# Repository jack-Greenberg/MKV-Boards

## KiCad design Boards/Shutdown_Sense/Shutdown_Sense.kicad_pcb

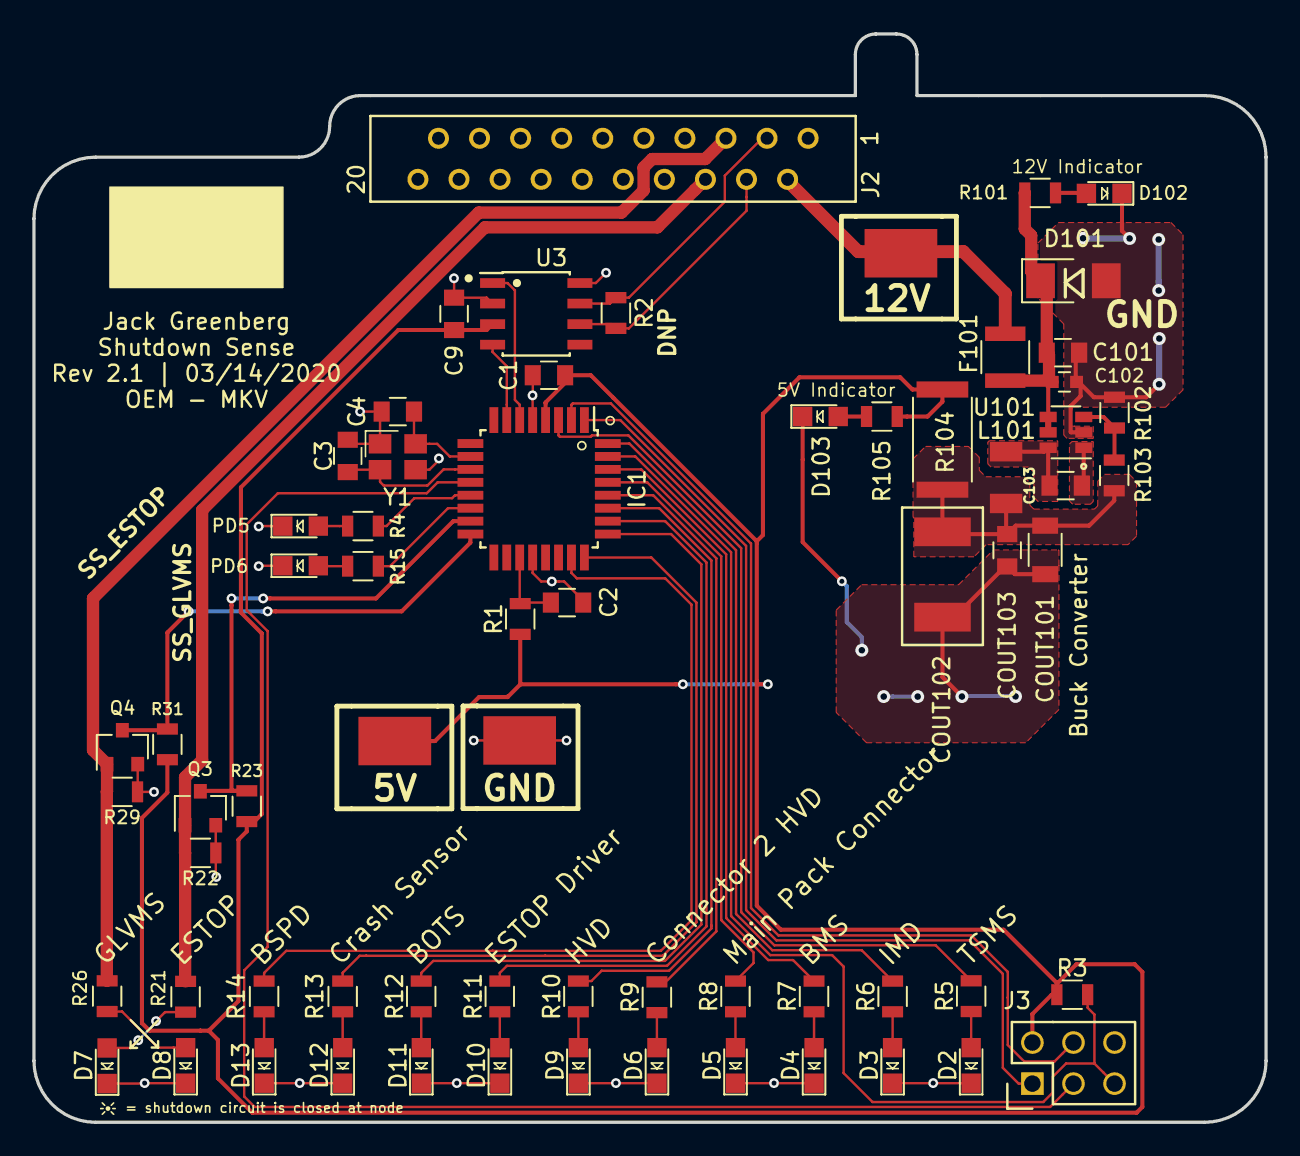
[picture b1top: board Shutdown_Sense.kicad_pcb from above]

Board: 2 copper layers, 76.2 x 67.3 mm, 67 parts (0 on the bottom side), 51 nets.

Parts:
C1, C9, C101, C103: C_0.1uF; C_0805_OEM
C2: C_100pF; C_0805_OEM
C3, C4: C_30pF; C_0805_OEM
C102: C_2.2uF; C_0603
COUT101: C_22uF; C_1206_OEM
COUT102: C_33uF; Fuse_1812
COUT103: C_47uF; C_0805_OEM
D2, D3, D4, D5, D6, D7, D8, D9, D10, D11, D12, D13, D102, D103: LED_0805; LED_0805_OEM
D101: D_Zener_18V; DO-214AA
F101: F_500mA_16V; Fuse_1210
IC1: ATMEGA16M1; TQFP-32_7x7mm_Pitch0.8mm
J2: MM_F_RA_20; micromatch_female_ra_20
J3: CONN_02X03; Pin_Header_Straight_2x03
L101: L_100uH
PD5, PD6: LED_0805; LED_0805_OEM
Q3, Q4: SSM3K333R; SOT-23F
R1: R_100; R_0805_OEM
R2: R_120_DNP; R_0805_OEM
R3: R_10k; R_0805_OEM
R4, R5, R6, R7, R8, R9, R10, R11, R12, R13, R14, R15, R105: R_200; R_0805_OEM
R21, R26, R101: R_1K; R_0805_OEM
R22, R29, R103: R_100K; R_0805_OEM
R23, R31: R_10K; R_0805_OEM
R102: R_25K; R_0805_OEM
R104: R_0_2512; R_2512_OEM
TP1, TP2, TP3: Test_Point_SMD
U3: CAN_Transceiver; SOIC-8_3.9x4.9mm_Pitch1.27mm_OEM
U101: TPS560430YF; SOT-23-6_OEM
Y1: Crystal_SMD; Crystal_SMD_FA238

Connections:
+12V: F101.2, J2.2, TP1.1
/CAN_high: J2.3, R2.1, U3.7
/CAN_low: J2.4, R2.2, U3.6
/DEBUG_LED_1: IC1.13, R4.1
/DEBUG_LED_2: IC1.14, R15.1
/MISO: IC1.1, J3.1
/MOSI: IC1.2, J3.4
/RESET: IC1.31, J3.5, R3.2
/RXCAN: IC1.7, U3.4
/SCK: IC1.12, J3.3
/SS_BMS: IC1.30, R7.2
/SS_BOTS: IC1.25, R12.2
/SS_BSPD: IC1.23, R14.2
/SS_Connector_2_HVD: IC1.28, R9.2
/SS_Crash_Sensor: IC1.24, R13.2
/SS_ESTOP: J2.5, Q4.1, R26.1, R29.1
/SS_ESTOP_Driver: IC1.26, R11.2
/SS_GLVMS: J2.6, Q3.1, R21.1, R22.1
/SS_HVD: IC1.27, R10.2
/SS_IMD: IC1.32, R6.2
/SS_Main_Pack_Connector: IC1.29, R8.2
/SS_TSMS: IC1.3, R5.2
/TXCAN: IC1.6, U3.1
/~SS_ESTOP_Pin: IC1.16, Q4.3, R31.2
/~SS_GLVMS_Pin: IC1.15, Q3.3, R23.2
GND: C1.2, C2.2, C3.2, C4.2, C9.2, C101.2, C102.2, COUT101.2, COUT102.2, COUT103.2, D2.1, D3.1, D4.1, D5.1, D6.1, D7.1, D8.1, D9.1, D10.1, D11.1, D12.1, D13.1, D101.2, D102.1, D103.1, IC1.5, IC1.20, J2.1, J2.7, J2.8, J2.9, J2.10, J2.11, J2.12, J2.13, J2.14, J2.15, J2.16, J2.17, J2.18, J2.19, J2.20, J3.6, PD5.1, PD6.1, Q3.2, Q4.2, R22.2, R29.2, R102.2, TP2.1, U3.2, U3.8, U101.2, Y1.2, Y1.4
unnamed: C2.1, IC1.19, R1.2
unnamed: C3.1, IC1.11, Y1.1
unnamed: C4.1, IC1.10, Y1.3
unnamed: C101.1, C102.1, D101.1, F101.1, R101.1, U101.4, U101.5
unnamed: C103.1, L101.1, U101.6
unnamed: C103.2, U101.1
unnamed: COUT101.1, COUT102.1, COUT103.1, L101.2, R103.1, R104.1
unnamed: PD5.2, R4.2
unnamed: D2.2, R5.1
unnamed: D3.2, R6.1
unnamed: D4.2, R7.1
unnamed: D5.2, R8.1
unnamed: D6.2, R9.1
unnamed: D7.2, R21.2
unnamed: D8.2, R26.2
unnamed: D9.2, R10.1
unnamed: D10.2, R11.1
unnamed: D11.2, R12.1
unnamed: D12.2, R13.1
unnamed: D13.2, R14.1
unnamed: PD6.2, R15.2
unnamed: D102.2, R101.2
unnamed: D103.2, R105.2
unnamed: R102.1, R103.2, U101.3
VCC: C1.1, C9.1, IC1.4, J3.2, R1.1, R3.1, R23.1, R31.1, R104.2, R105.1, TP3.1, U3.3

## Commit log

2020-04-22 Fix SR-latch language in BSPD schematic
